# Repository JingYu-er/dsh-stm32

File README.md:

# dsh-stm32

STM32 全流程工具层，以 [DeepSeek Harness (DSH)](https://github.com/deepseek-ai/deepseek-harness) 插件形式分发：40 个工具、7 条斜杠命令与 1 个随包下发的 SKILL，把「工具链探测 → 建工程 → 改 `.ioc`（含时钟）→ 生成代码 → 编译 → 烧录 → 调试 → 回读寄存器」这条链交给模型执行，另含串口交互（Windows）与会话内的「调试台」面板。

在支持范围内，同一套工具从 F1 到 H7 用法一致；遇到不支持的芯片或功能，调用时会直接说明缺什么，不会给出一份猜出来的结果。

| 能力面 | 覆盖范围 |
| --- | --- |
| 芯片族 | 27 个族：C0 / F0 / F1 / F2 / F3 / F4 / F7 / G0 / G4 / H5 / H7 / L0 / L1 / L4 / L4+ / L5 / MP1 / MP2 / N6 / U0 / U3 / U5 / WB / WB0 / WBA / WL / WL3 |
| HAL 建工程 | 21 个单核族：C0 / F0 / F1 / F2 / F3 / F4 / F7 / G0 / G4 / H5 / H7 / L0 / L1 / L4 / L4+ / L5 / U0 / U3 / U5 / WBA / WL |
| 寄存器建工程 | 21 族，均通过 create→build 编译矩阵 |
| 时钟规划 | 18 族；其中 PLL1 为 H5 / U5 / WBA / L4+ |
| `.ioc` 外设预设 | 按 CubeMX 官方数据派生：串口 / TIM PWM / ADC |
| 寄存器名与位域 | F1 |

**English:** [README_EN.md](./README_EN.md)

[快速开始](#快速开始最小验证空目录到灯在闪) · [工具参考](#工具参考) · [斜杠命令](#斜杠命令) · [调试台](#调试台面板) · [配置](#配置) · [已知限制](#已知限制) · [排错](#排错) · [规格书](docs/dsh-stm32-plugin-规格.md)

## 它能做什么

多数「让 AI 编写 STM32 代码」的方案止于代码层：产出一段 `main.c`，能否编译、烧录后灯是否按预期闪烁，仍要在 CubeMX、终端与调试器之间手工确认。模型看不到板子，也就无法对结果负责。

本插件把硬件侧接入 DSH：`.ioc` 可读可改（事务 + 回滚），代码只写入 `USER CODE` 块，生成与编译返回真实报错行，烧录不与调试器抢占探针，烧录后读回寄存器状态。每一步都有可核对的结果（计划编号、`文件:行:列`、`Verified OK`、`GPIOC.ODR` 的 bit13，有寄存器表时直接给出 `ODR13=1`），模型据此决定下一步。

| 环节 | 手工流程 | 本插件 |
| --- | --- | --- |
| 建工程 | GUI 配置时钟树、引脚与工程参数，生成 CMake，手写 `launch.json` | `stm32_project_create` 约 2 秒产出模板工程（与 CubeMX GUI 产物一致，`.vscode` 内两份配置就位） |
| 改配置 | GUI 修改后重新生成，担心 `USER CODE` 丢失 | `stm32_ioc_plan` 先出差异（不写盘）→ 确认 → `stm32_ioc_apply` 带校验、备份与失败回滚 |
| 写代码 | 整文件编辑，易写入生成区，重新生成后丢失 | `stm32_code_patch` 只写 `USER CODE` 块，块外逐字节保留 |
| 编译 | Keil，或自行维护 CMake 与 VS Code 任务 | `/stm32-build [目录] [--clean]` |
| 烧录 | Keil，或手写 `tasks.json` 调 openocd | `/stm32-flash [目录]` |
| 验证 | 断点调试，手工查看寄存器 | `stm32_regs_read` 回读状态：`GPIOC.ODR` 两次采样确认计数递增，`AFIO.MAPR` 确认 SWD 未被固件关闭 |
| 调试 | 按 F5 手动下断点，结束再关会话 | `stm32_debug_run` 停在 `main` 抓取一次现场后释放探针；连续调试才开 `stm32_debug_session`，空闲自动关闭 |

## 安装

### 安装插件

只需先具备 DSH 本体，工具链可以稍后补。

```powershell
dsh plugin --profile desktop add dsh-stm32
```

`dsh plugin` 等价于在 profile 目录执行 `pnpm add`，并把 `dsh-stm32` 写入该 profile 的 `dsh.profile.bundles`。安装后完全退出 DSH 再启动（插件层只在进程启动时加载）。

- 校验：`dsh plugin --profile desktop why dsh-stm32` 显示 `0.1.8`
- 卸载：`dsh plugin --profile desktop remove dsh-stm32`，随后重启 DSH
- 装到 Web：把 `desktop` 换成 `web`

### 补齐工具链

插件装好后即可解析 `.ioc`、查看引脚 / 时钟 / 中断、预览计划；真正编译、烧录、调试时才需要编译器与探针工具。

| 要做什么 | 需要什么 | 怎么补 |
| --- | --- | --- |
| 编译 | `arm-none-eabi-gcc`、`cmake`、`ninja` | `/stm32-setup` 一条命令装齐（MSYS2 + 工具链，约 300 MB），或自行安装后由插件自动发现 |
| 烧录、调试 | `openocd`、`arm-none-eabi-gdb`（或 `gdb-multiarch`）、CMSIS-DAP / ST-Link 探针 | 同上；探针驱动由系统识别，无需额外配置 |
| 生成代码、建 HAL 工程 | STM32CubeMX（含内置 JRE）与其固件包 | 从 ST 官网安装 CubeMX（需 ST 账号），插件自动定位安装位置；固件包在 CubeMX 包管理器内安装 |

不确定缺什么时，先看诊断：

```text
/stm32-env      # 编译 / 烧录 / 调试 / 生成四项能力逐项列出缺件、安装位置与安装方式
/stm32-setup    # 先出计划，确认后执行安装，结束后自检
```

`/stm32-env` 在没有装任何工具链时也能用：它只执行版本查询，不写盘、不联网。

### 开工前检查

```text
/stm32-doctor
```

只读体检：工具链是否齐备、是否有残留的 openocd / gdb 进程占用探针、gdb 端口是否被占用、工程内 `.elf` 与 `.ioc` 是否就位、`.ioc` 是否存在会导致烧录后失联的配置。

### 内置资源

芯片型号到启动文件、设备宏、Flash / RAM 容量的映射，以及 `.ioc` 模板、链接脚本与寄存器表，随插件一起分发，安装后离线可用，不需要下载资源包。`stm32_assets verify` 校验完整性；报缺文件时按提示重装插件即可。

### 从源码安装

仅开发或需要改代码时使用。`npm install` 与 `npm run build` 的说明见[开发与测试](#开发与测试)。

```powershell
git clone https://github.com/JingYu-er/dsh-stm32.git
cd dsh-stm32
npm install --no-audit --no-fund   # 仅安装 typescript
npm run build                      # tsc -> lib/，提交前必须执行
```

挂载到 profile 时用 `link:`，不要用 `file:`：

```powershell
cd "$env:USERPROFILE\.dsh\profiles\desktop"
pnpm add "link:D:\path\to\dsh-stm32"

# 在同一目录的 package.json 中把 "dsh-stm32" 追加到 dsh.profile.bundles
# 随后重启 dsh（插件层只在进程启动时加载）
```

原因：`nodeLinker: hoisted` 下 `file:` 会被复制成真实目录，重新编译出的 `lib/` 不会被宿主读取，表现为「改完代码、重启仍为旧行为」。`link:` 读取工作区里的 `lib/`，改完仍需重启 DSH 重新加载。

## 快速开始：最小验证（空目录到灯在闪）

这条链路已在真板验证，全程由模型调用工具完成。各步使用同一套工具，闪灯只是最小样例。

| 步 | 动作 | 工具 | 实测耗时 |
| --- | --- | --- | --- |
| 1 | 体检：工具链、被占用探针、端口、`.elf`、`.ioc` 告警 | `stm32_doctor` | 约 2 秒 |
| 2 | 空目录建 CMake 工程骨架（含已配置 SWD 的 `.ioc`） | `stm32_project_create` | 约 2 秒 |
| 3 | 按 `.ioc` 无头运行 CubeMX，产物落到 `Core/` | `stm32_generate` | 首次 130–175 秒；`.ioc` 与产物未变时跳过（小于 1 秒） |
| 4 | 编译（首次自动 `cmake --preset`） | `stm32_build` | 配置约 5 秒 + 编译 3 秒 |
| 5 | 只烧录：program + verify + reset | `stm32_flash` | 2.1–2.6 秒 |
| 6 | 回读 `GPIOC.ODR`（或地址 `0x4001100C`），确认状态翻转 | `stm32_regs_read` | 0.4–1.3 秒 |

第 6 步的符号写法依赖内置寄存器表；安装不完整时可改用地址 `0x4001100C`，报告中不会有寄存器名与位域解释。

模型侧只需一句：「在 `D:\work\blink` 建一个 STM32F103C8T6 的闪灯工程，编译并烧录」。

最小验证覆盖「建工程 → 生成 → 编译 → 烧录 → 回读」整条链路，没有闪灯专用步骤；真实项目走同一链路，差异在于 `.ioc` 里的外设数量、`USER CODE` 块数量与代码规模。

| 完整项目中的操作 | 路径 | 验证状态 |
| --- | --- | --- |
| 外设配置：GPIO / 定时器 / USART / I2C / SPI / ADC / DMA / 中断 | `stm32_ioc_plan`（GPIO 按芯片引脚表校验）→ `stm32_ioc_apply` → `stm32_generate` | GPIO、时钟、SWD 已上板实测；其余外设机制相同，未逐项实测 |
| 新增外设后补 HAL 源 | 在 `cmake/stm32cubemx/CMakeLists.txt` 的 `STM32_Drivers_Src` 中加入 `stm32f1xx_hal_<外设>.c`，或写入 `cmake/user/CMakeLists.txt` | 需手工补齐：插件只放置 `Src/` 与 `Inc/`，CubeMX 生成的 `cmake/**` 不搬运 |
| 多源文件与自定义模块 | 写入 `cmake/user/CMakeLists.txt`，模板已留位置 | 位置就位，未单独实测 |
| 业务代码 | `stm32_code_patch` 按块写入，重新生成时按标签搬回 | 已实测（追加 / 替换；标签写错时会列出全部可用标签） |
| 调参、改时钟 | `.ioc` 事务：先出差异 → 校验 → 备份 → 失败回滚 | 已实测 |
| 确认外设运行 | `stm32_regs_read` 读任意外设寄存器：符号名 `TIM2.CNT` / `USART1.SR` / `ADC1.DR`，或物理地址 `0x40000024`；只写外设名 `GPIOC` 时输出该外设全部寄存器 | 地址写法已上板实测；符号名与位域复测中 |
| 查看现场 | `stm32_debug_run` 停在 `main` 抓取一次；连续调试用 `stm32_debug_session` + `stm32_debug_eval` | 已实测（停在 `main () at main.c:67`） |

边界集中在[已知限制](#已知限制)：HAL 建工程覆盖 21 个单核族，寄存器建工程覆盖 21 族（验证板为 C8T6），宿主仅在 Windows 验证，探针默认 CMSIS-DAP，新增外设需手工补 HAL 源。外设种类不受工具限制：`.ioc` 里能配置的能力都走同一链路；除闪灯外的外设尚未逐项上板实测，正式开工前建议先执行 `/stm32-doctor`。

## 工具参考

### 环境与工程

| 工具 | 用途 |
| --- | --- |
| `stm32_doctor` | 只读体检：工具链是否齐备、是否有残留 openocd / gdb、gdb 端口是否占用、`.elf` 与 `.ioc` 是否就位；按芯片输出能力与已知问题 |
| `stm32_route_plan` | 按具体工程与需求评估 HAL 路线与寄存器路线的开发代价，并区分可自动安装与需人工安装的缺件 |
| `stm32_env_install` | 安装 MSYS2 与工具链组件（gcc / gdb / openocd / cmake / ninja），默认只出计划，`dryRun:false` + `confirm:true` 才执行；只写用户级 PATH，不请求管理员权限 |
| `stm32_download` | 只下载不安装：J-Link 官方直链 + 校验和；CubeMX / CubeProgrammer 打开官方页或校验本地文件 |
| `stm32_firmware_install` | 下载并组装 STM32Cube 固件包，优先官方压缩包，失败回退 GitHub 拼包；默认只出计划 |
| `stm32_assets` | 查看、校验、清理包内资源（芯片数据、`.ioc` 模板、链接脚本、启动文件、寄存器表） |
| `stm32_cache` | 查看、校验、拉取、清理下载缓存（寄存器版 CMSIS 模板） |
| `stm32_project_create` | 建工程：`route:"hal"` 用模板 + 固件包，`route:"register"` 建不依赖 CubeMX 的寄存器工程；两条路线均生成 `openocd.cfg` |
| `stm32_project_export` | 工程打包为 zip，默认排除 `build/`、`.dsh-stm32/`、`node_modules/`、`.git/`，可附编译产物 |

### `.ioc`：查看与修改

| 工具 | 用途 |
| --- | --- |
| `stm32_ioc_inspect` | 只读解析：型号、引脚、信号、使能外设、中断、时钟树、工程设置与风险提示 |
| `stm32_ioc_plan` | 计算逐键差异（不写盘）：支持外设预设、引脚、中断、调试口、时钟规划与批量置键 |
| `stm32_ioc_apply` | 写入计划：源文件校验 → 备份 → 原子替换；支持按备份回滚 |
| `stm32_ioc_verify` | 由 CubeMX 自己重读 `.ioc`，指出被静默丢弃的外设与缺失的初始化 |

### 流程图规则

`diagram` 是功能框架，不是逐元件原理图：

- 按功能聚合：主控、NFC 天线与标签、光检测、供电、调试接口、按键；模块内部连接不画线。
- 连线只在模块之间，标签归纳为 I2C / SPI / UART / ADC / LED / PWM / SWD 这类总线名。
- 电源网络（VCC、GND）单独列出，不进连线；端点过多的网络同样不进框图。
- 布局由插件生成：主控居中、模块绕环，连线从面对对方的一侧进出，能直不拐。

这些规则同时写在插件的技能文本里，读图与画图用的是同一套口径。

### 原理图（KiCad 10）

| 工具 | 用途 |
| --- | --- |
| `stm32_sch_read` | 只读解析 KiCad 工程：图纸树、元件、网络、电源网络，以及模块框图（哪两块电路相连、走什么总线） |
| `stm32_sch_pins` | 主控引脚矩阵：每个脚的网络名、类型、是否悬空，并按 CubeMX 数据库给出可复用信号候选 |
| `stm32_sch_check` | 检查原理图本身，并与 `.ioc`、`.kicad_pcb` 对账：缺值、缺封装、SWD / BOOT0 / 电源缺失、网络被拆开 |
| `stm32_sch_to_ioc` | 把引脚连接转成 `.ioc` 配置草案：每个脚给出建议信号、置信度与候选，纯 GPIO 网络给输入/输出建议；硬件复用对不上时给软件模拟退路与代价；只读，不写 `.ioc` |

版本范围是 KiCad 10（`version 20260306`）。元件库内嵌在图纸里，不要求安装 KiCad，也不读 `sym-lib-table`；只跟随根图纸引用到的子图，`.history/` 与其他历史版本不参与解析。对账判据是连通性：同一 PCB 网络上的焊盘，在原理图里必须属于同一网络；名字不一致只作提示。工具只读，不改原理图，也不改工程配置；`stm32_sch_to_ioc` 的草案要交给 `stm32_ioc_plan` 才落盘，且对不上库信号的脚会列在待确认里。

### 电路设计（tscircuit + KiCad）

在 `hardware/` 下用 tscircuit 写电路，导出真 KiCad 工程，再用 KiCad 自己的检查器验收。检查按嘉立创常规工艺进行：线宽与间距 ≥ 0.2 mm、孔径 ≥ 0.3 mm、丝印字高 ≥ 0.8 mm，规则写进工程的 `.kicad_dru`，报出来的是「能不能按这一档打板」，并附打样成本估算。

| 工具 | 用途 |
| --- | --- |
| `stm32_ecad_init` | 建 `hardware/{circuit,kicad,libs,out}` 与最小 `package.json`；依赖需要在该目录执行 `npm install` |
| `stm32_ecad_build` | 用 KiCad 自带的 bun 跑 `tsci build`：`.circuit.tsx` → `circuit.json`、SVG 与 `kicad/*.kicad_sch|.kicad_pcb`；并把 `tscircuit:` 生成名换回真库名（`footprint="kicad:…"` 时），官方封装复制进 `hardware/libs`；立创封装（`footprint="jlcpcb:C…"`）按位号固化进库并记在 `libs/sources.json` |
| `stm32_ecad_check` | 先补齐工程库表与嘉立创工艺规则（`<工程>.kicad_dru`），再跑 `kicad-cli sch erc` 与 `pcb drc`，把违规收敛成规则、级别与涉及项清单；顺带报出未命名网络、板子尺寸、最细走线、最小孔径与打样成本 |
| `stm32_ecad_libs` | 把生成工程里内嵌的封装/符号抽成 `hardware/libs` 下的真库，并补齐 `fp-lib-table` / `sym-lib-table` |
| `stm32_ecad_step` | 导出 STEP 到 `hardware/out`；先按「官方 3D 目录 → `hardware/libs/3d` → 缓存」解析模型并改写路径，缺模型只报告，不阻断导出 |
| `stm32_ecad_export` | 一次导出 Gerber、钻孔、贴片坐标与 STEP 到 `hardware/out`，按最小可下单集合汇总 |
| `stm32_ds_fetch` | 把非 STM32 器件的数据手册抓到本地缓存：按立创编号、按本工程用到的器件，或手工导入 PDF |
| `stm32_ds_lookup` | 按用途查手册：引脚、绝对最大额定值、电气特性、时序、封装——给页号、标题与该页开头正文 |
| `stm32_ds_list` | 列出本地手册缓存：编号、型号、占用、抓取时间与来源 |
| `stm32_pdf_read` | 读 PDF：`info` 看页数与文字层、`text` 取指定页文字（保版面，表格可读）、`figures` 列图与表、`table` 把参数表切成行列、`render` 把页面或局部渲染成 PNG 交给视觉读图 |
| `stm32_ecad_package` | 把 `hardware/` 打成可交付 zip（跳过 `node_modules`、`dist`、`.history`），写完读回自检 |

写者只有一个：`.kicad_sch` / `.kicad_pcb` 由 tscircuit 生成，插件只读。tscircuit 把符号与封装内嵌在工程里、名字归到 `tscircuit` 之类的生成名，检查前会先导出成 `hardware/libs` 下的真库并补齐库表，否则报告里只剩「库不在配置中」这类环境噪音；未命名网络（`.R1 > .pin1 to .C1 > .pin1`）会单独列出并给出 `<net name="VDD" />` 的修法。构建要求 KiCad 10 与其自带的 `bun.exe`；首次 `npm install` 约 730 MB，之后构建一般 15–40 秒。板子上的元件优先用 KiCad 官方库（`footprint="kicad:..."`），需要时再用立创编号兜底。

### 代码与构建

| 工具 | 用途 |
| --- | --- |
| `stm32_code_patch` | 只写 `USER CODE BEGIN/END` 块内内容，块外逐字节保留；写前备份 |
| `stm32_generate` | 无头运行 CubeMX，产物落到 `Core/`，`USER CODE` 按标签搬回；`.ioc` 未变时跳过 |
| `stm32_build` | 编译：自动推断构建目录与 `.elf`，返回错误行、警告数、FLASH / RAM 占用；可转出 hex / bin |

### 烧录、调试与运行时

| 工具 | 用途 |
| --- | --- |
| `stm32_flash` | 只烧录：program + verify + reset，烧完释放探针；烧前检查 Serial Wire；失败时给出探针错误的分类与处理建议 |
| `stm32_debug_run` | 烧录后停在 `main`，抓取寄存器、调用栈与局部变量，随后复位运行并释放探针 |
| `stm32_debug_session` | 开启长调试会话（空闲与总时长受限），供 `stm32_debug_eval` 连续使用 |
| `stm32_debug_eval` | 在调试会话中执行 gdb 命令：读变量、寄存器、调用栈、内存 |
| `stm32_debug_stop` | 关闭调试会话并释放探针 |
| `stm32_regs_read` | 按地址或符号名读寄存器，有寄存器表时解析位域；读取时短暂暂停，读完继续运行，不复位芯片 |
| `stm32_watch` | 登记表达式并采样（含差值）；`kind=write/read/access` 装为硬件观察点，受芯片观察点数量限制 |
| `stm32_rtt` | RTT 通道：固件侧把控制块放在 RAM，主机侧经 openocd 读取，输出带级别与时间戳 |
| `stm32_serial` | 串口交互（Windows）：`list` / `open` / `read` / `send` / `transact` / `status` / `close` |

### 固件中的 RTT 接入（最短示例）

```c
/* USER CODE BEGIN 0 */
static char rtt_buf[3][1024];
static void rtt_init(void) {
  /* 控制块按 SEGGER 约定放在 RAM：acId / acName / 三个环，见 templates/ 中的 rtt.h */
}
/* USER CODE END 0 */
```

完整实现见 `templates/` 内的 RTT 模板；通道数与环大小由 `RTT_UP_CHANNELS` / `RTT_BUF_SIZE` 控制（默认 3×1 KB = 3 KB `.bss`，C8T6 只有 20 KB RAM）。

### PDF 读取（数据手册与原理图）

依赖 poppler（`pdftotext` / `pdfinfo` / `pdftoppm`）：`pacman -S --needed mingw-w64-ucrt-x86_64-poppler` 装进 MSYS2，`stm32_doctor` 会显示版本。

| 用途 | 调法 | 得到什么 |
| --- | --- | --- |
| 判断这份 PDF 能不能读文字 | `mode=info` | 页数、纸张、有无文字层；描边字体的 PDF 会明确提示只能看图 |
| 查参数、读表格 | `mode=text` + `first`/`last` | 保版面的文字，表格按列对齐 |
| 找「第几页有什么图」 | `mode=figures` | 图注清单与页号 |
| 读某个参数表的行与列 | `mode=table` | 列名、行数据、置信度；切不全是 medium，配同页原文核对 |
| 看曲线、框图 | `mode=render` + `page`/`dpi`/`crop` | PNG 路径，交给视觉读图；抠数字用 300–400 dpi 并收紧裁切 |

读图得到的是形态与量级（约 ±0.5 个最小刻度），不是精确数值；精确参数优先查同页表格。

### 数据手册缓存

非 STM32 器件（LDO、运放、传感器、接口芯片）第一次用到时，把厂商手册抓下来存本地：

- `stm32_ds_fetch code=C25137` 按立创编号抓；`all=true` 抓本工程 `circuit` 源码里出现的全部 `jlcpcb:` 器件；`file=` 手工导入 PDF（反爬或没有编号时的退路）。
- 缓存位置 `~/.dsh-stm32/datasheets/<编号>/`（`meta.json` + 以内容 sha256 命名的 PDF），可用 `DSH_STM32_DATASHEETS` 改目录。命中缓存时**不联网**；抓取失败记 24 小时负缓存，`refresh=true` 可强制重试。
- `stm32_ecad_build` 成功后会自动补齐本工程用到的手册；面板「电路设计」头部显示「手册 2/3」，缺的标黄，点「补手册」走同一套逻辑。
- `stm32_ds_lookup code=C25137 kind=electrical` 直接翻到电气特性那一页：先读前 40 页建一次索引（只记页号），之后按页取正文。
- `stm32_ds_list` 看已缓存哪几份、占多少空间。
- 抓到之后直接 `stm32_pdf_read file=C25137`（或写型号）就能读，不必再给路径——引脚、电气参数、时序都从这里取，不靠记忆编。

## 斜杠命令

| 命令 | 说明 |
| --- | --- |
| `/stm32-doctor` | 体检：工具链、残留进程、端口、`.elf` 与 `.ioc` 告警 |
| `/stm32-env` | 工具链体检：编译 / 烧录 / 调试 / 生成四项能力缺什么、装在哪、如何安装 |
| `/stm32-setup` | 体检 → 安装计划 → 确认后安装 → 自检 |
| `/stm32-build [目录] [--clean]` | 编译（CMake + Ninja，默认 `build/Debug`），`--clean` 先全清 |
| `/stm32-flash [目录]` | 只烧录：program + verify + reset，结束后释放探针 |
| `/stm32-debug [目录]` | 烧录并进入调试，停在 `main`，之后可用 `stm32_debug_eval` |
| `/stm32-stop` | 关闭调试会话、释放探针，之后可在 VS Code 中按 F5 |

## 调试台（面板）

会话页签内的「调试台」用于人机同看同一条时间线：`stm32_*` 调用的开始、成功、失败与耗时，以及串口、RTT、监视、引脚、时钟、中断与 `.ioc` 变更。

| 页签 | 内容 | 操作 |
| --- | --- | --- |
| 概览 | 工程、型号、SYSCLK、容量、调试会话、工具链、构建与烧录、证据占用、告警摘要 | 跳转失败筛选与实时通道，导出操作记录 Markdown |
| 事件 | 调用起止、耗时、慢调用标记、参数摘要 | 只看失败、按工具筛选、按耗时排序、批量引用、导出 JSONL、事件深链 |
| 实时通道 | 串口 / RTT / 监视输出 | 暂停、清空、关键字过滤、RTT 级别过滤、发送串口行、常驻采集、导出 |
| 引脚 | 按外设分组、按端口排布、按封装画法（芯片型号 + 封装名 + 四边引脚小长条，1 脚圆点） | 筛选、复制引用、查看 `.ioc` 键、导出 CSV |
| 流程图 | 按功能模块聚合的网状框图（主控居中，NFC 天线与标签、光检测、供电、调试口、按键环绕摆放），连线从框的四个方向进出，按总线与信号用途标注，附检查结论 | 只读；元件不单独成框，电源网络单独列出 |
| 电路设计 | tscircuit 工作区状态：初始化、依赖、入口、最近构建、库、导出产物 | 可在页签里直接触发构建、检查、导出库、导出 STEP、打包 Gerber、打包交付、补数据手册；构建与打包要几十秒 |
| 时钟 | 树与流向两种视图、各节点频率与分频 | 超限标记与「改为 ÷N」建议（按父时钟计算） |
| 中断 | NVIC 使能、抢占与子优先级 | 筛选、排序、就地修改、批量修改 |
| 故障 | 失败事件原文、规则解码、按规则合并 | 分类筛选、复制组提示、导出 CSV |
| 产物 | elf / hex / bin、大小、校验和、容量、两次构建对比 | 复制校验和 |
| 变更 | `.ioc` 与基线的差异 | 记基线、恢复单键、一次恢复全部 |

工程目录按约定解析，位置可显式指定：程序目录取 `program/`、`firmware/`、`app/`、`user/` 或工程根；KiCad 工程取 `hardware/`、`kicad/`、`hw/`、`pcb/`（都没有时按深度 2 内扫描 `*.kicad_pro`）；配置与基线在工程根的 `.dsh-stm32/`。两处位置可写进工程根的 `dsh-stm32.conf`（`firmware=` / `hardware=`），不再依赖目录名推断。

打开面板会先补齐本会话最近的记录，之后实时追加。事件每 30 秒写入 `~/.dsh-stm32/evidence/<日期>/<会话>/`，可回放、导出；默认保留 7 天、最近 20 个会话，可在配置里调整。面板只展示本插件自己的工具调用，不含其他工具的调用。面板只显示本会话的工程与调试会话：换到另一个工作区的会话时，没有工程就是空面板，不会借用别的会话的工程与调试输出。

## 串口（Windows）

`stm32_serial` 提供七个动作：`list` / `open` / `read` / `send` / `transact` / `status` / `close`。打开端口后由插件持有，一次一个端口，默认 115200 8N1、无流控、DTR / RTS 不拉高，回合结束时自动关闭。

- 平台：仅 Windows；Linux 与 macOS 返回 `unsupported-platform`。
- 端口：`list` 枚举可用端口；端口参数按设备记忆，换 COM 号后可复用。
- 读：`read` 支持游标，只返回游标之后的新行。
- 写入：`send` 发送一行，`transact` 发送并等待匹配回包（正则）。
- 保留：`persist=true` 跨回合保留端口。

参考验证板为 CH340（`1A86:7523`，COM5，115200）。同一板上的 DAPLink 虚拟串口（`c251:f001`，COM4）不承载应用串口数据。

## 设计要点

- **只写自有文件**：`.ioc` 走事务（计划 → 校验 → 备份 → 替换），生成区只写 `USER CODE` 块，其余生成文件不由插件修改。
- **烧录与调试分离**：`stm32_flash` 不建立调试会话，烧完即释放探针；需要调试时才开 `stm32_debug_session`，空闲自动关闭，避免与 VS Code 抢占探针。
- **结论附证据**：失败时给出编译器 `文件:行:列`、探针错误分类、寄存器读数，而不是模糊描述。
- **缺什么就说什么**：芯片、时钟或调试脚本不受支持时，报错直接说明缺哪一项，不猜测、不静默跳过。
- **不接管宿主**：面板只展示状态与执行明确的工程动作，不做代码编辑与 Git 操作。

## 配置

### 配置文件（`~/.dsh-stm32/config.json`）

工具链位置由插件维护：`stm32_env_install` 安装后写入该文件，后续工具直接读取，无需重启 DSH 或设置环境变量。也可手工编辑：

```json
{
  "version": 1,
  "msys64": "E:/msys64",
  "binDirs": [],
  "packages": ["mingw-w64-ucrt-x86_64-arm-none-eabi-gcc", "mingw-w64-ucrt-x86_64-cmake"],
  "cubeMxRoot": "",
  "updatedAt": "2026-02-01T00:00:00.000Z"
}
```

`binDirs` 为空时由 `msys64` 推导 `<msys64>/ucrt64/bin`。文件损坏（JSON 非法）视为不存在，不影响其他功能。

优先级：工具参数（`binDirs` / `cubeMxRoots`）> 环境变量 > 配置文件 > 内置默认值。内置默认值只含 Windows 常见位置，不含任何机器专属路径。

### 设置面板

DSH 设置内的「STM32 工具链」页提供三张卡片：

- **装在哪**：读取并保存 `msys64` / `cubeMxRoot` / 额外 `binDirs`，保存后下一条工具调用即生效。
- **缺什么**：执行一次探测（只读版本查询），逐项显示路径、版本、缺失原因，以及编译 / 烧录 / 调试 / 生成四项能力徽章。
- **装工具链**：先出计划（步骤、下载体积、PATH 与配置变更），确认后执行；过程显示步骤与日志尾部。

### 下载缓存与固件包

- 寄存器版 CMSIS 模板首次使用时下载到缓存（默认 `%LOCALAPPDATA%\dsh-stm32\cache`），之后复用；逐文件校验，变更即拒收。`stm32_cache` 可查看、校验、拉取与清理。
- HAL 路线使用本机 CubeMX 固件包：F1 默认 `STM32Cube_FW_F1_V1.8.7`，其他族取已安装的最高版本；可用 `firmwarePackage` 指定。缺失时先在 CubeMX 包管理器中安装，或用 `stm32_firmware_install` 下载组装。
- `stm32_download` 只下载或校验安装包（默认目录 `%LOCALAPPDATA%\dsh-stm32\downloads`），不执行安装器，不请求管理员权限。

### 环境变量（可选）

| 变量 | 作用 | 默认 |
| --- | --- | --- |
| `STM32_BIN_DIRS` | 工具链目录候选，`;` 分隔，整份替换内置列表（自动发现仍追加在尾部） | `C:/msys64/ucrt64/bin`、`C:/msys64/mingw64/bin` |
| `STM32_CUBEMX_ROOT` | CubeMX 安装根，整份替换内置列表 | `C:/Program Files/STMicroelectronics/STM32Cube/STM32CubeMX` |
| `STM32_NO_DISCOVER` | 设为 `1` 关闭自动发现（仅用内置列表） | 不设 |
| `DSH_STM32_CONFIG` | 替换配置文件路径 | `%USERPROFILE%\.dsh-stm32\config.json` |
| `DSH_STM32_NO_CONFIG` | 设为 `1` 完全不读配置文件 | 不设 |
| `DSH_STM32_CACHE` | 下载缓存根目录，支持 `~` | `%LOCALAPPDATA%\dsh-stm32\cache` |
| `DSH_STM32_DOWNLOADS` | 安装包下载目录，支持 `~` | `%LOCALAPPDATA%\dsh-stm32\downloads` |
| `DSH_STM32_HOME` | 插件数据根目录（配置、证据、快照、备忘） | `%USERPROFILE%\.dsh-stm32` |
| `DSH_STM32_EVIDENCE` | 证据目录 | `~/.dsh-stm32/evidence` |
| `DSH_STM32_EVIDENCE_FLUSH_SECONDS` | 证据落盘间隔（5–3600 秒） | 30 |
| `DSH_STM32_EVIDENCE_KEEP_DAYS` | 证据保留天数（0–365，0 = 不清理） | 7 |
| `DSH_STM32_EVIDENCE_KEEP_SESSIONS` | 证据保留会话数（1–200） | 20 |
| `DSH_STM32_SNAPSHOTS` | `.ioc` 基线目录 | `~/.dsh-stm32/ioc-snapshots` |
| `DSH_STM32_OFFLINE` | 设为 `1` 禁止联网下载（模板与固件包仅用本地缓存） | 不设 |
| `MSYS2_MIRROR` | 安装包镜像，必须与 `MSYS2_INSTALLER_SHA256` 同时设置 | 官方 → TUNA → NJU → 阿里云 |
| `MSYS2_INSTALLER_URL` / `MSYS2_INSTALLER_SHA256` | 覆盖安装包地址与校验和，必须成对设置 | 官方固定版本 |
| `DSH_STM32_JLINK_URL` / `DSH_STM32_JLINK_SHA256` | 覆盖 J-Link 直链与校验和，必须成对设置 | SEGGER 官方 |

工具参数与上述变量等价：烧录与调试类接受 `binDirs`、`elfPath`、`buildDir`、`configFile`、`adapterSpeed`；生成与建工程类接受 `cubeMxRoots`、`firmwarePackage`。

工具链位置通常无需配置：未指定 `binDirs` / `STM32_BIN_DIRS` 时，插件会在常见位置查找并追加候选——`<盘>/msys64`、`<盘>/msys2`、`<盘>/app/msys64`、`<盘>/tools/msys64`、`%LOCALAPPDATA%/Programs/msys64` 下的 `ucrt64/bin`、`mingw64/bin`、`clang64/bin`，以及 `STM32CubeMX_PATH` 环境变量、CubeMX 卸载登记项、`Program Files\STMicroelectronics\STM32Cube` 等位置下的 CubeMX。找不到时，错误与 `stm32_doctor` 会列出已检查的目录。

### openocd.cfg（工程内优先）

CMSIS-DAP（默认）：

```text
source [find interface/cmsis-dap.cfg]
source [find target/stm32f1x.cfg]
adapter speed 4000
```

ST-Link：

```text
source [find interface/stlink.cfg]
transport select hla_swd
source [find target/stm32f1x.cfg]
```

工程内没有 `openocd.cfg` 时按 `.ioc` 的芯片族选择调试脚本（F1 → `stm32f1x`、F4 → `stm32f4x`、G4 → `stm32g4x`；L4 与 L4+ 共用 `stm32l4x`）。C0 / U0 的脚本随插件提供并在建工程时复制到工程的 `openocd/` 目录；H5 / N6 / U3 / WBA / WB0 / WL3 / MP2 暂无脚本，烧录会被明确拒绝。

### `.ioc` 的两个硬要求

1. **SYS 调试口为 Serial Wire**（PA13 = `SYS_JTMS-SWDIO`、PA14 = `SYS_JTCK-SWCLK`）；缺失时用 `stm32_ioc_plan` 的 `serialWire: true` 补齐。
2. **`ProjectManager.KeepUserCode=true`**；否则重新生成时 `USER CODE` 内容不保留。

## 已知限制

| 限制 | 说明 | 处理方式 |
| --- | --- | --- |
| 仅在 Windows 验证 | 生成代码依赖 CubeMX 的 Windows 安装形态 | 暂无可替代方案；烧录、调试、读寄存器在其他平台理论可用，未验证 |
| 部分芯片暂无官方调试脚本 | C0 / U0 用插件自带的适配脚本（未上板验证）；H5 / N6 / U3 / WBA / WB0 / WL3 / MP2 暂无脚本 | 烧录前会明确说明，不会静默失败 |
| HAL 建工程不覆盖双核与 MPU 系列 | 双核 WB、MP1 / MP2 / N6、WB0 / WL3 不在范围内 | 建工程时直接说明不支持 |
| 深层能力按族分级 | HAL 21 族、寄存器 21 族、时钟 18 族；寄存器名与位域目前只有 F1 | 缺哪项就在调用时说明哪项 |
| 探针按 USB 实见选择 | ST-Link、DAPLink / CMSIS-DAP、J-Link 自动区分；工程内 `openocd.cfg` 优先 | 需要固定选择时手写 `openocd.cfg` |
| 新增外设需手工补 HAL 源 | 插件只放置 `Src/` 与 `Inc/`，CubeMX 生成的 `cmake/**` 不搬运 | 修改 `STM32_Drivers_Src` 或写入 `cmake/user/CMakeLists.txt` |
| 生成与建工程需要 CubeMX 与对应固件包 | F1 默认 `STM32Cube_FW_F1_V1.8.7` | 传 `firmwarePackage`，或先在 CubeMX 内安装固件包 |
| RTT 仅通道 0，帧头为自定义格式 | 13 字节头（长度 + 级别 + 时间戳 + UTF-8 正文） | 用级别过滤；结构化内容写入正文；通道与环大小见 `rtt.h` |
| 串口仅 Windows | 不含推流、自动重连，一次一个端口 | 使用系统串口工具，或等待后续版本 |
| 寄存器名与位域依赖内置寄存器表 | 目前覆盖 F1 的 100 / 101 / 102 / 103 / 105 / 107 | 使用 `0x` 开头的地址；`stm32_assets verify` 检查安装完整性 |

## 排错

| 现象 | 原因 | 处理 |
| --- | --- | --- |
| 插件未加载 | profile 的 `dsh.profile.bundles` 未包含 `dsh-stm32`，或未重启 | 重装并重启 DSH；用 `dsh plugin --profile desktop why dsh-stm32` 校验 |
| 修改代码后行为未变 | 用 `file:` 安装，宿主读取的是拷贝 | 改用 `link:`，重新 `npm run build` 并重启 DSH |
| 报缺工具链 | 未安装或路径未收录 | 先跑 `/stm32-env` 看缺什么，再 `/stm32-setup` 安装；或手工设置 `binDirs` |
| 烧录报探针占用 | 其他调试器（VS Code、残留 openocd）持有探针 | `/stm32-stop`，关闭其他调试器后重试；`stm32_doctor` 会列出残留进程 |
| 烧录后 SWD 失联 | `.ioc` 未启用 Serial Wire | 用 `stm32_ioc_plan` 的 `serialWire: true` 补齐后重新生成并烧录 |
| 生成后外设被丢弃 | `.ioc` 键与外设推导不一致 | 用 `stm32_ioc_verify` 让 CubeMX 诊断 |
| 面板空白或数据不更新 | 服务端改动未重启，或 `lib` 比进程新 | 完全退出 DSH 再启动；面板状态条会提示「有新构建」 |
| 串口无数据 | 端口选择错误（如选到 DAPLink 虚拟串口） | `stm32_serial list` 确认端口；应用串口通常在 CH340 等 USB 转串口设备上 |

## 开发与测试

| 命令 | 作用 |
| --- | --- |
| `npm run build` | `tsc` 编译到 `lib/`，并复制客户端与数据资源 |
| `node test/run-units.mjs` | 离线单测：81 个套件 / 1101 个用例，不需要板子 |
| `node .dsh-stm32/acceptance.mjs` | 本机验收脚本：面板 API、事件流、证据、产物、故障、中断、串口与探针 |
| `npm run test:pack` | 打包 tarball、解包、用解包产物实际建一次寄存器工程 |
| `npm run test:size` | 包体与资产护栏 |

发布形态：随包发布的内容限定在 `package.json` 的 `files`（`lib`、`client`、`templates`、`assets`、`docs/reading-guide.md`、`cordis.patch.yml`、两份 README、`LICENSE`）。开发用的 `docs/`、`test/`、`scripts/` 不进包。

开发调试用的环境变量（日常使用无需设置）：`DSH_STM32_ASSETS`、`DSH_STM32_FACTS` 覆盖资源目录，`DSH_STM32_SERIAL_BRIDGE`、`DSH_STM32_SERIAL_POWERSHELL` 覆盖串口桥路径，`DSH_STM32_PYTHON` 指定解析用的 Python 解释器。

## 目录结构

```text
src/
  index.ts          插件入口：注册工具、斜杠命令、面板 API 与 SKILL
  tools/            40 个工具的注册与参数校验
  engine/           引擎：工程、.ioc、生成、构建、烧录、调试、事件与面板 API
  data/             芯片数据、CubeMX 数据、时钟、搜索根、工具链配置
  commands/         7 条斜杠命令
  skill/            随包下发的 stm32-workflow SKILL
client/client.js    面板源码（纯 JS + react，无打包器）
lib/                tsc 产物与复制后的资源（随包发布）
assets/             芯片数据、.ioc 模板、链接脚本、启动文件、寄存器表
templates/          建工程模板、寄存器模板、串口桥与 RTT 模板
test/               80 个离线套件与 e2e 脚本
scripts/            构建、打包、体积与冒烟脚本
docs/               开发笔记、精读指南、规格书、图表
```

## 文档

- [规格书](docs/dsh-stm32-plugin-规格.md)：工具契约、状态机、验收判定标准
- [开发笔记](docs/development-notes.md)：里程碑、宿主契约问题、各工具实现细节与实测数据
- [源码精读指南](docs/reading-guide.md)：分层阅读顺序、文件职责与关键导出、流程图与不变量
- 发布说明：按版本随发布页提供，历史见 git 历史与开发笔记
- 可视化：[架构总览](docs/diagrams/dsh-stm32-architecture.html) / [主线旅程](docs/diagrams/dsh-stm32-journey.html)（单文件 HTML，离线可开）

## 许可证

[MIT](LICENSE)

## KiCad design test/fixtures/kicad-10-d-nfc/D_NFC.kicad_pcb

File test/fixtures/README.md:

# 测试夹具

离线单测（`node test\run-units.mjs`）只依赖这里，不依赖开发机上的真实工程，
所以任何人 `git clone` 下来都能跑：

| 文件 | 用途 |
| --- | --- |
| `project/demo.ioc` | 8 引脚 + RCC + SWD 的 STM32F103C8T6 配置，`ioc-units` / `ioc-plan-units` / `schema-guard` 用它 |
| `scratch.ioc` | 只有 Ports、`MainLocation=Src` 的另一种形状，验证解析器不靠特例 |
| `project/openocd.cfg` | `flash-units` 验证"优先用工程里的 cfg" |
| `project/CMakePresets.json` + `project/build/Debug/CMakeCache.txt` | `build-units` 验证按 preset 与 `build/*/` 两种方式找构建目录 |
| `project/build/Debug/demo.elf` | **占位文件**（4 KB 的 0），只为验证 `.elf` 的定位与大小判断，不可烧录 |
| `project/Core/Src/main.c`、`project/_scratch/Src/main.c` | `engine-units` 用真实 CubeMX 产物验证 USER CODE 合并（含标签缺失上报） |
| `svd/stm32c031-excerpt.svd` | `facts-units`/`facts-acquire-units` 的黄金 SVD 切片（FLASH_ACR/OPTR/SECR 全字段+枚举） |
| `rm-facts-c0.json` | EN RM0490 Rev 6 自动抽取的 10 条 C0 语义（带页码/引文/appliesTo 六线）；`build-facts` 与黄金样本用它。中文 Rev 1 旧版备份在仓外 `demo/.dsh-stm32/rm-facts-c0.zh-Rev1.bak-2026-11-07` |
| `rm/`（5 份） | `rm-sources-units` 离线夹具：sitemap 样本、stmcu 分类/详情页样本（真实形状截取）、微型 EN/CID 假 PDF（覆盖判定与表格间距回归） |

会话类用例（`session-units`）不读磁盘上的工具链：它用 `fixtures.mjs` 的 `fakeBinDirs()` 在系统临时目录里造一个假工具链目录（空文件占位的 `openocd` / `gdb-multiarch` / `arm-none-eabi-gcc`），因此没装 msys64 的机器也能跑。

唯一真依赖 CubeMX 的是 `scaffold-patch-units` 里两条用例，它们带 `existsSync` 判定的 `skip:`，没有 CubeMX 时显示为 skipped 而不是失败。

需要真板子或真 CubeMX 的 e2e（`test/e2e-*.mjs`）不吃这套夹具，它们用环境变量指路：

- `DSH_STM32_E2E_PROJECT`：一个可编译、可烧录的 STM32 工程（默认 `fixtures/project`，但那个不能烧）；
- `DSH_STM32_E2E_ROOT`：放临时副本的目录（默认系统临时目录）。

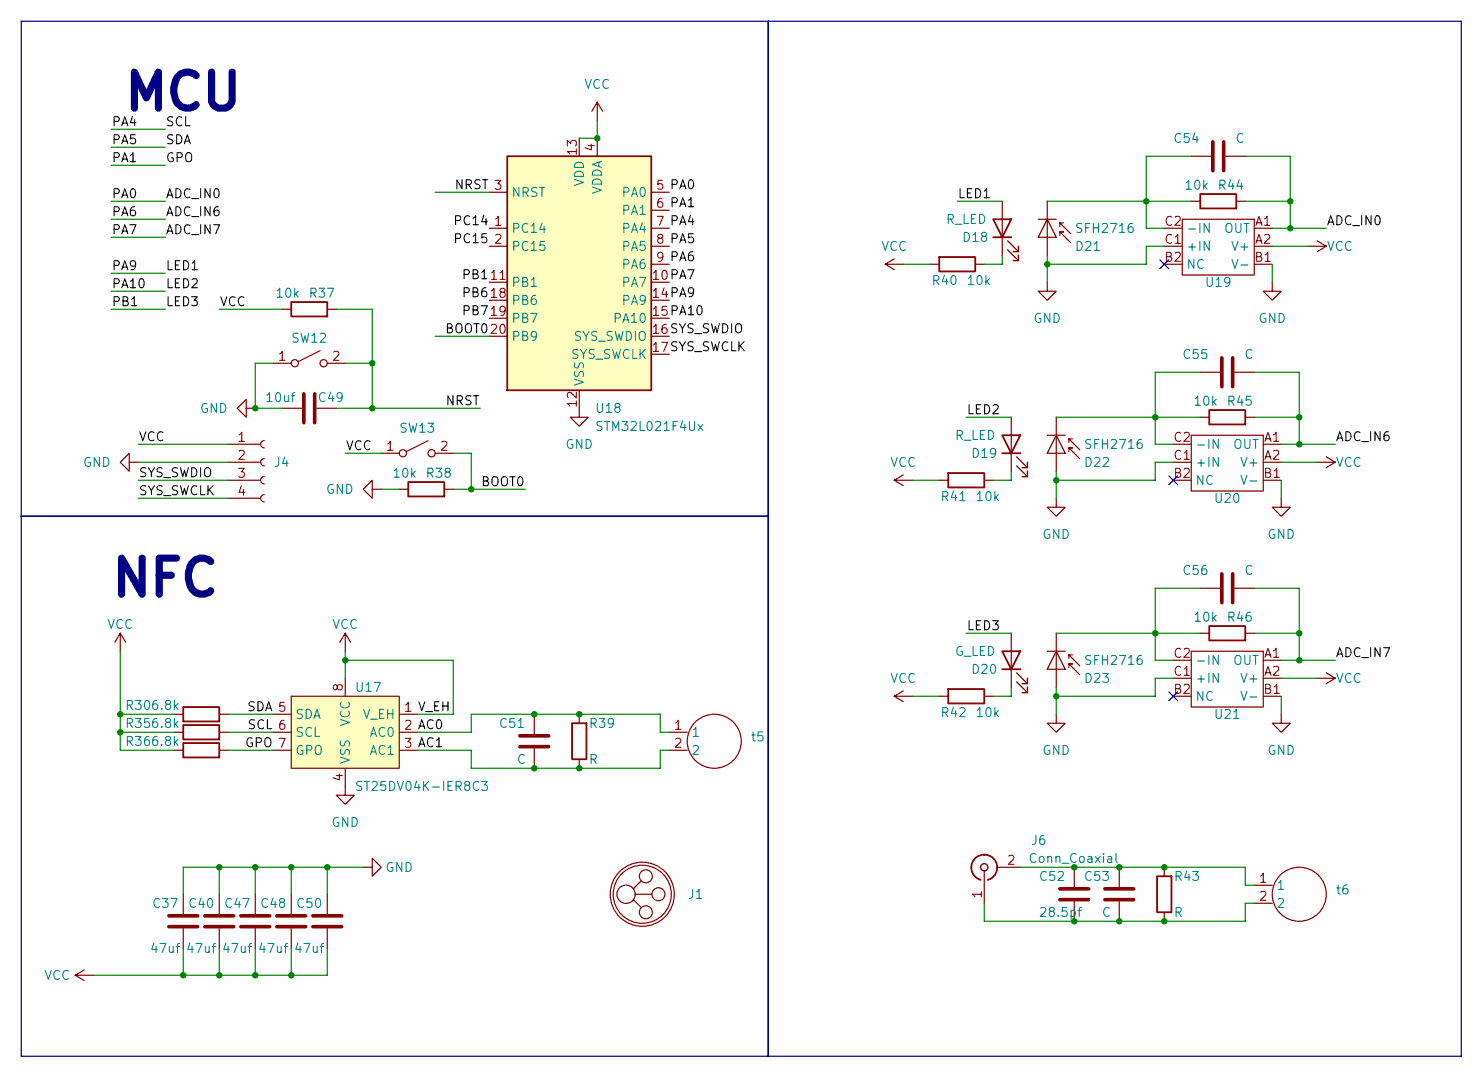
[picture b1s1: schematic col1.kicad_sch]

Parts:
C37, C40, C47, C48, C50: 47uf; C_0402_1005Metric
C49: 10uf; R_0201_0603Metric
C51: C; C_0201_0603Metric
C52: 28.5pf; C_0603_1608Metric
C53, C54, C55, C56: C; C_0603_1608Metric
D18, D19: R_LED; LED_0402_1005Metric
D20: G_LED; LED_0402_1005Metric
D21, D22, D23: SFH2716; LED_0805_2012Metric
J1: D-微流控nfc可绘制区域
J4: Conn_01x04_Socket; JST_GH_BM04B-GHS-TBT_1x04-1MP_P1.25mm_Vertical
J6: Conn_Coaxial; SMA_Amphenol_132134-14_Vertical
R30, R35, R36: 6.8k; R_0201_0603Metric
R37, R38, R40, R41, R42, R44, R45, R46: 10k; R_0201_0603Metric
R39: R; R_0201_0603Metric
R43: R; R_0603_1608Metric
SW12, SW13: SW_SPST; SW_SPST_B3U-1000P
U17: ST25DV04K-IER8C3; DFN-8-1EP_3x2mm_P0.5mm_EP1.36x1.46mm
U18: STM32L021F4Ux; ST_UFQFPN-20_3x3mm_P0.5mm
U19, U20, U21: WLCSP-6_1.46x1.1mm_Layout3x2_P0.4mm_反向
t5, t6: 30.048mm-13.56Mhz

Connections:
/col1/AC0: C51.1, R39.2, U17.2 (AC0), t5.1
/col1/AC1: C51.2, R39.1, U17.3 (AC1), t5.2
/col1/ADC_IN0: C54.2, R44.2, U18.5 (PA0), U19.A1 (OUT)
/col1/ADC_IN6: C55.2, R45.2, U18.9 (PA6), U20.A1 (OUT)
/col1/ADC_IN7: C56.2, R46.2, U18.10 (PA7), U21.A1 (OUT)
/col1/BOOT0: R38.2, SW13.2 (B), U18.20 (PB9)
/col1/GPO: R36.2, U17.7 (GPO), U18.6 (PA1)
/col1/LED1: D18.2 (A), U18.14 (PA9)
/col1/LED2: D19.2 (A), U18.15 (PA10)
/col1/LED3: D20.2 (A), U18.11 (PB1)
/col1/NRST: C49.2, R37.2, SW12.2 (B), U18.3 (NRST)
/col1/PA4: R35.2, U17.6 (SCL), U18.7 (PA4)
/col1/PA5: R30.2, U17.5 (SDA), U18.8 (PA5)
/col1/PB6: U18.18 (PB6)
/col1/PB7: U18.19 (PB7)
/col1/PC14: U18.1 (PC14)
/col1/PC15: U18.2 (PC15)
/col1/SYS_SWCLK: J4.4, U18.17 (SYS_SWCLK)
/col1/SYS_SWDIO: J4.3, U18.16 (SYS_SWDIO)
GND: C37.2, C40.2, C47.2, C48.2, C49.1, C50.2, D21.2 (A), D22.2 (A), D23.2 (A), J4.2, R38.1, SW12.1 (A), U17.4 (VSS), U18.12 (VSS), U19.B1 (V-), U19.C1 (+IN), U20.B1 (V-), U20.C1 (+IN), U21.B1 (V-), U21.C1 (+IN)
unnamed: D18.1 (K), R40.1
unnamed: D19.1 (K), R41.1
unnamed: D20.1 (K), R42.1
unnamed: C54.1, D21.1 (K), R44.1, U19.C2 (-IN)
unnamed: C55.1, D22.1 (K), R45.1, U20.C2 (-IN)
unnamed: C56.1, D23.1 (K), R46.1, U21.C2 (-IN)
unnamed: C52.1, C53.1, J6.2 (Ext), R43.2, t6.1
unnamed: C52.2, C53.2, J6.1 (In), R43.1, t6.2
VCC: C37.1, C40.1, C47.1, C48.1, C50.1, J4.1, R30.1, R35.1, R36.1, R37.1, R40.2, R41.2, R42.2, SW13.1 (A), U17.1 (V_EH), U17.8 (VCC), U18.4 (VDDA), U18.13 (VDD), U19.A2 (V+), U20.A2 (V+), U21.A2 (V+)

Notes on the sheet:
MCU
NFC

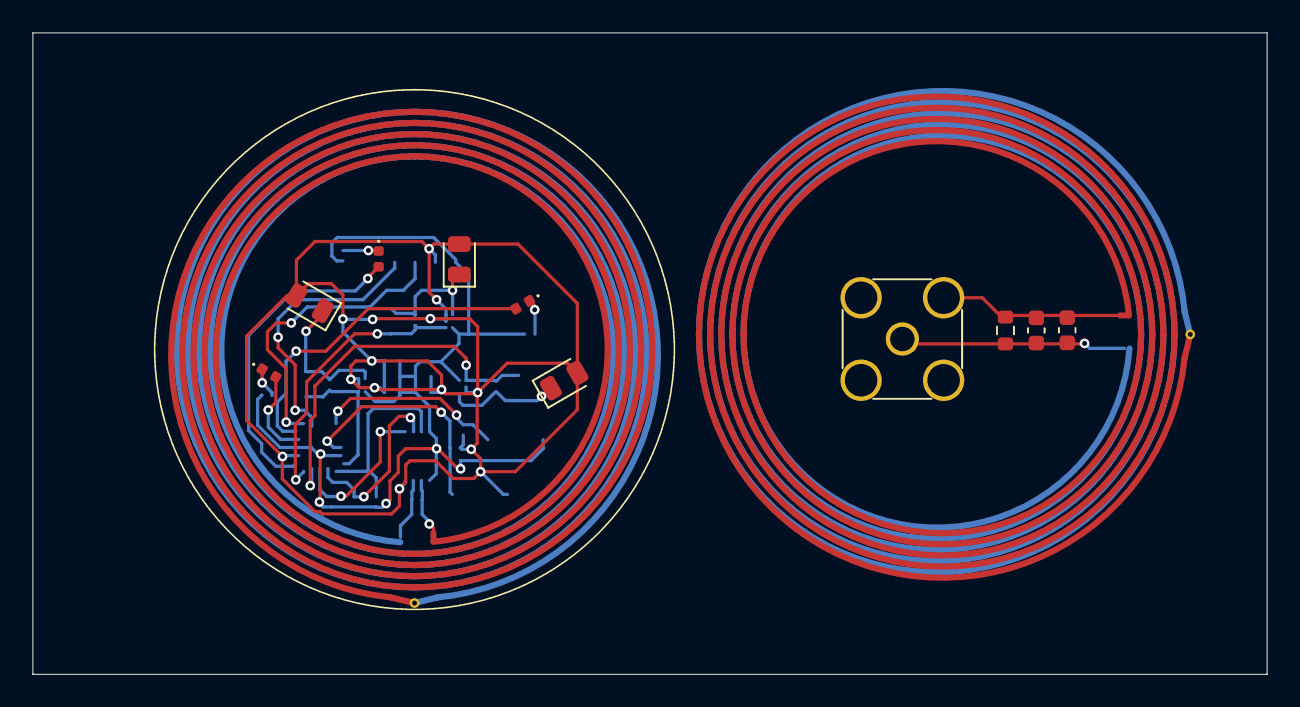
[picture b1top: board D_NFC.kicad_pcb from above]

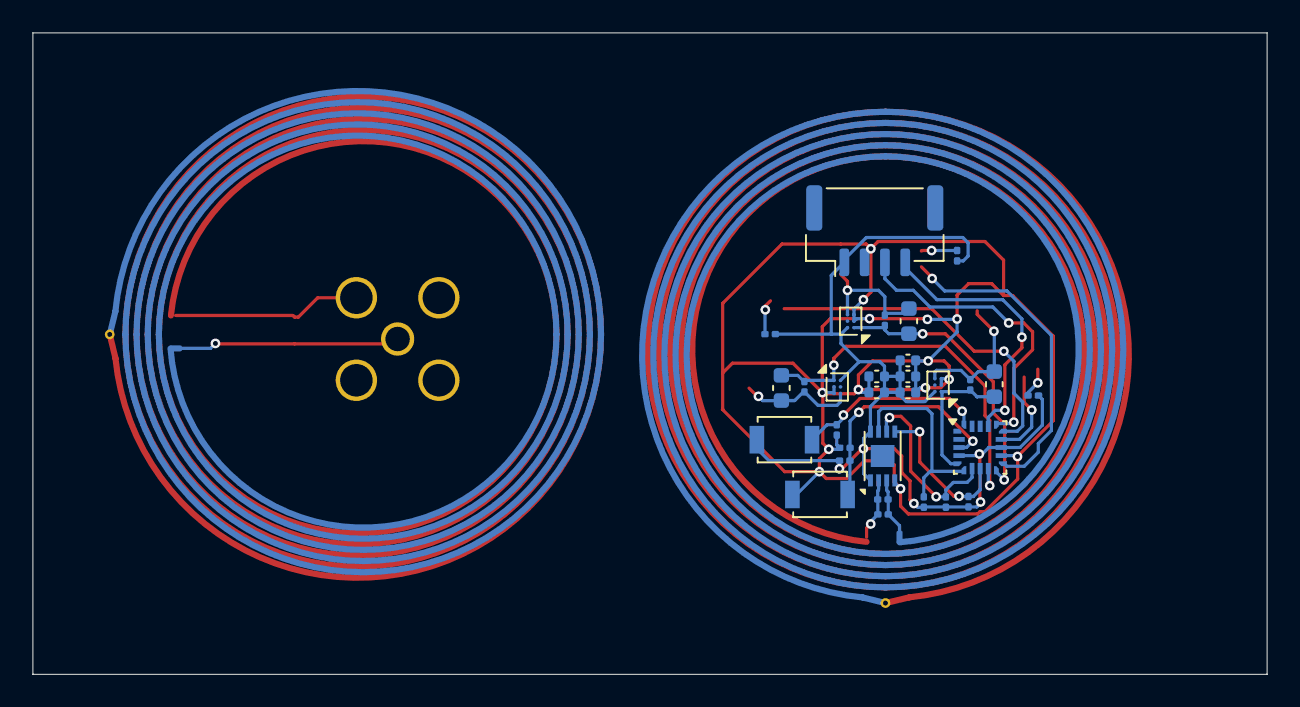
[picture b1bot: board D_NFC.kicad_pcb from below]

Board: 2 copper layers, 76.0 x 39.5 mm, 43 parts (30 on the bottom side), 25 nets.
